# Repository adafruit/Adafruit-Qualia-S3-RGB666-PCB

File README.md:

## Adafruit Qualia ESP32-S3 for TTL RGB-666 Displays PCB

<a href="http://www.adafruit.com/products/5800"><br/>
Click here to purchase one from the Adafruit shop</a>

PCB files for the Adafruit Qualia ESP32-S3 for TTL RGB-666 Displays.

Format is EagleCAD schematic and board layout
* https://www.adafruit.com/product/5800

### Description

There's a few things everyone loves: ice cream, kittens, and honkin' large TFT screens. We're no strangers to small TFT's - [from our itsy 1.14" color display](https://www.adafruit.com/search?q=1.14+tft) that graces many-a-TFT-Feather to [our fancy 3.5" 320x480](https://www.adafruit.com/product/2050) breakout screen. But most people who dabble or engineer with microcontrollers know that you sort of 'top out' at 320x480 - that's the largest resolution you can use with every day SPI or 8-bit 8080 interfaces. After that, you're in TTL-interface TFT land, where displays no longer have an internal memory buffer and instead the controller has to continuously write scanline data over a 16 or 18 or 24 pin interface.

RGB TTL interface TFT displays can get big: they start out at around 4.3" diagonal 480x272, and can get to 800x480, 800x600 or even 720x720. For displays that big, you need a lot of video RAM (800x480 at 24 bit color is just over 1MB), plenty of spare GPIO to dedicate, and a peripheral that will DMA the video RAM out to the display continuously. This is a setup familiar to people working with hefty microcontrollers or microcomputers, the sort of device that run cell phones, or your car's GPS navigation screen. But until now, nearly impossible to use on low cost microcontrollers.

The ESP32-S3 is the first low-cost microcontroller that has a built in peripheral that can drive TTL displays, and can come with enough PSRAM to buffer those large images. For example, on the **Adafruit Qualia ESP32-S3 for TTL RGB-666 Displays**, we use a S3 module with 16 MB of Flash and 8 MB of octal PSRAM. Using the built in RGB display peripheral you can display graphics, images, animations or even video (cinepak, natch!) with near-instantaneous updates since the whole screen gets updated every ~30FPS.

This dev board is designed to make it easy for you to explore displays that use the "secondary standard' 40-pin RGB-666 connector. This pin order is most commonly seen on square, round and bar displays. [You'll want to compare the display you're using to this datasheet](https://cdn-shop.adafruit.com/product-files/5792/Specification_TL021WVC02CT-B1323B.pdf), if it matches you'll probably be good! One nice thing about this connector ordering is that it also includes pins for capacitive touch overlay, and we wire those up to the ESP32-S3's I2C port so you can also have touch control with your display.

**Don't forget! This is just the development board, a display is not included.** Use any RGB-666 pinout display with or without a touch overlay. Note that you will need to program in the driver initialization code, dimensions, and pulse widths in your programming language. Here are some known-working displays that you can use in Arduino or CircuitPython:

- [2.1" 480x480 Round with Capacitive Touch](https://www.adafruit.com/product/5792)
- [2.1" 480x480 Round without touch](https://www.adafruit.com/product/5806)
- [4" 720x720 Square with Capacitive Touch](https://www.adafruit.com/product/5794)
- [4" 720x720 Round without touch](https://www.adafruit.com/product/5793)
- [4.6" 960x320 Rectangular Bar](https://www.adafruit.com/product/5805)

On the Qualia board we have the S3 modules, with 16 pins connected to the TFT for 5-6-5 RGB color, plus HSync, VSync, Data Enable and Pixel Clock. There's a constant current backlight control circuit using the [TPS61169](https://www.ti.com/product/TPS61169/part-details/TPS61169DCKR) which can get up to 30V forward voltage and can be configured for 25mA-200mA in 25mA increments (default is 25mA). Power and programming is provided over a USB C connector, wired to the S3's native USB port. For debugging, the hardware UART TX pin is available as well.

Since almost every GPIO is used, and almost all RGB-666 displays need to be initialized over SPI, we put a [PCA9554](https://www.ti.com/product/PCA9554) I/O expander on the shared I2C bus. Arduino or CircuitPython can be instructed on how to use the expander to reset and init the display you have if necessary. The remaining expander pins are connected to two right-angle buttons, and the display backlight.

The expander is what lets us have a full 4-pin SPI port and two more analog GPIO pins - [enough to wire up an MMC in 1-wire SDIO mode along with an I2S amplifier to make an A/V playback demo](https://www.youtube.com/watch?v=pEjw-bCQ-lQ). Maybe we can even eat ice cream while watching kitten vids! There is also the shared I2C port, we provide a Stemma QT / Qwiic port for easy addition of any sensor or device you like.

### License

Adafruit invests time and resources providing this open source design, please support Adafruit and open-source hardware by purchasing products from [Adafruit](https://www.adafruit.com)!

Designed by Limor Fried/Ladyada for Adafruit Industries.

Creative Commons Attribution/Share-Alike, all text above must be included in any redistribution.
See license.txt for additional details.

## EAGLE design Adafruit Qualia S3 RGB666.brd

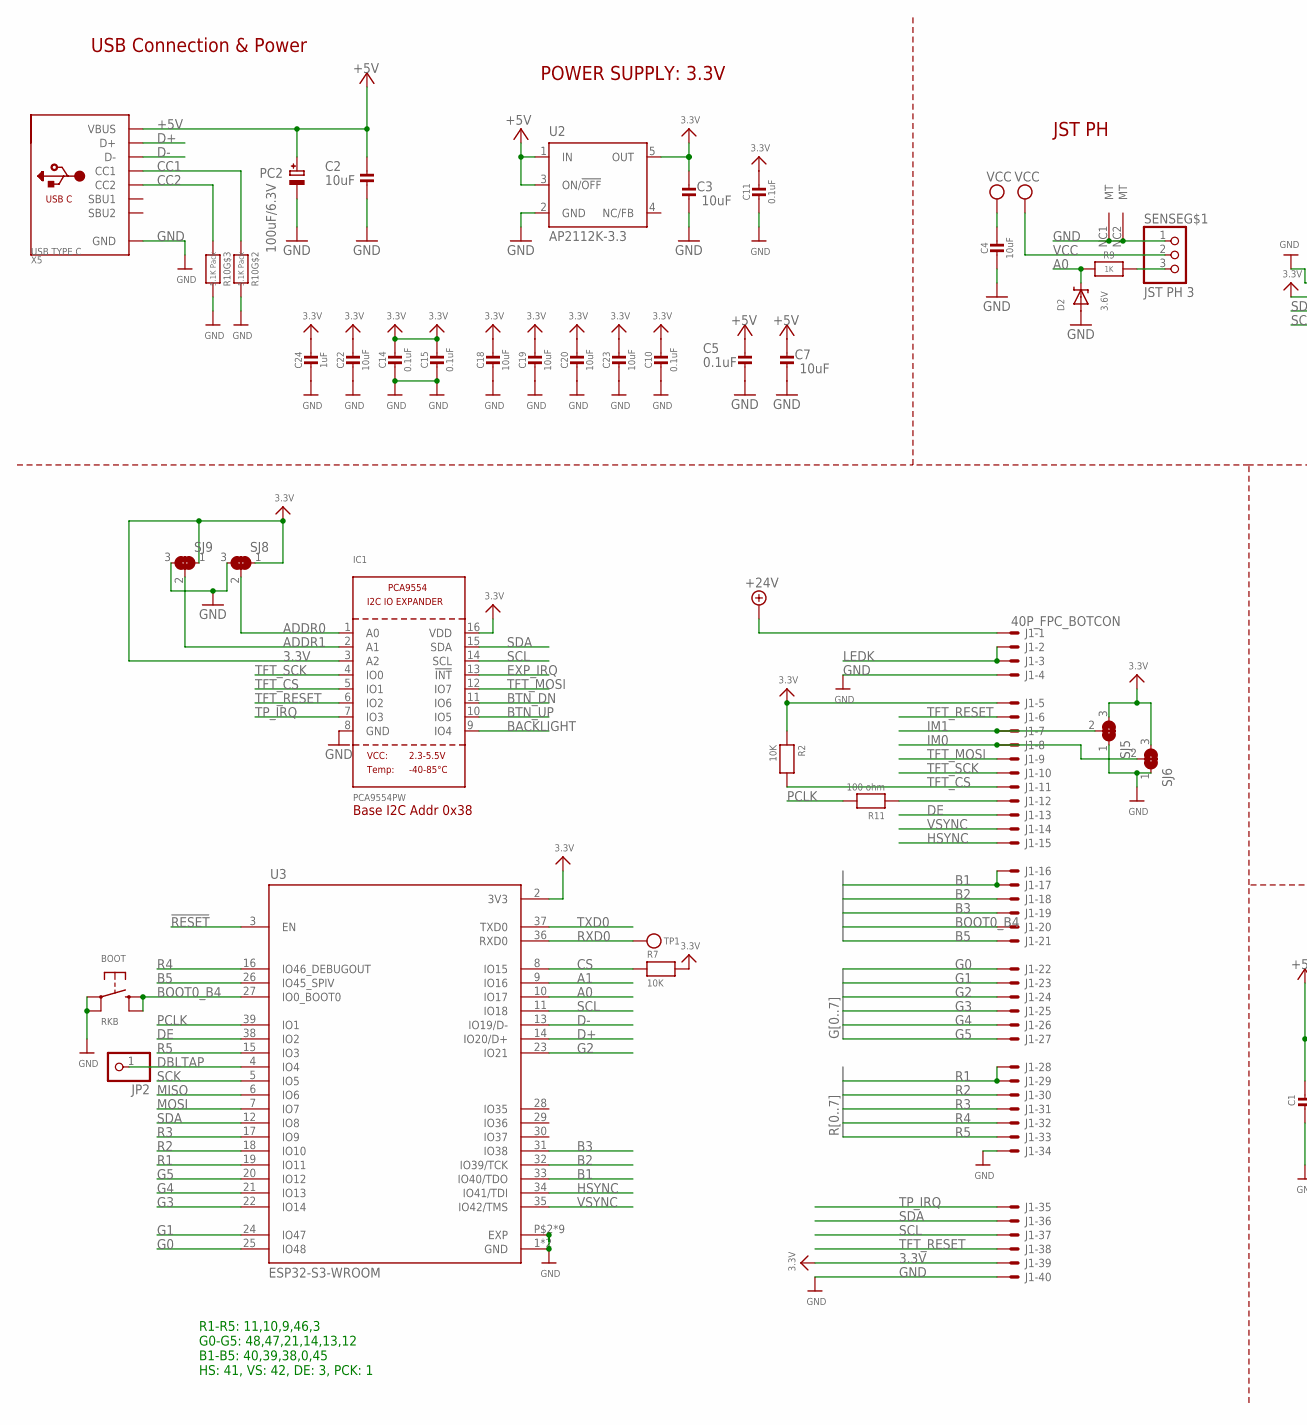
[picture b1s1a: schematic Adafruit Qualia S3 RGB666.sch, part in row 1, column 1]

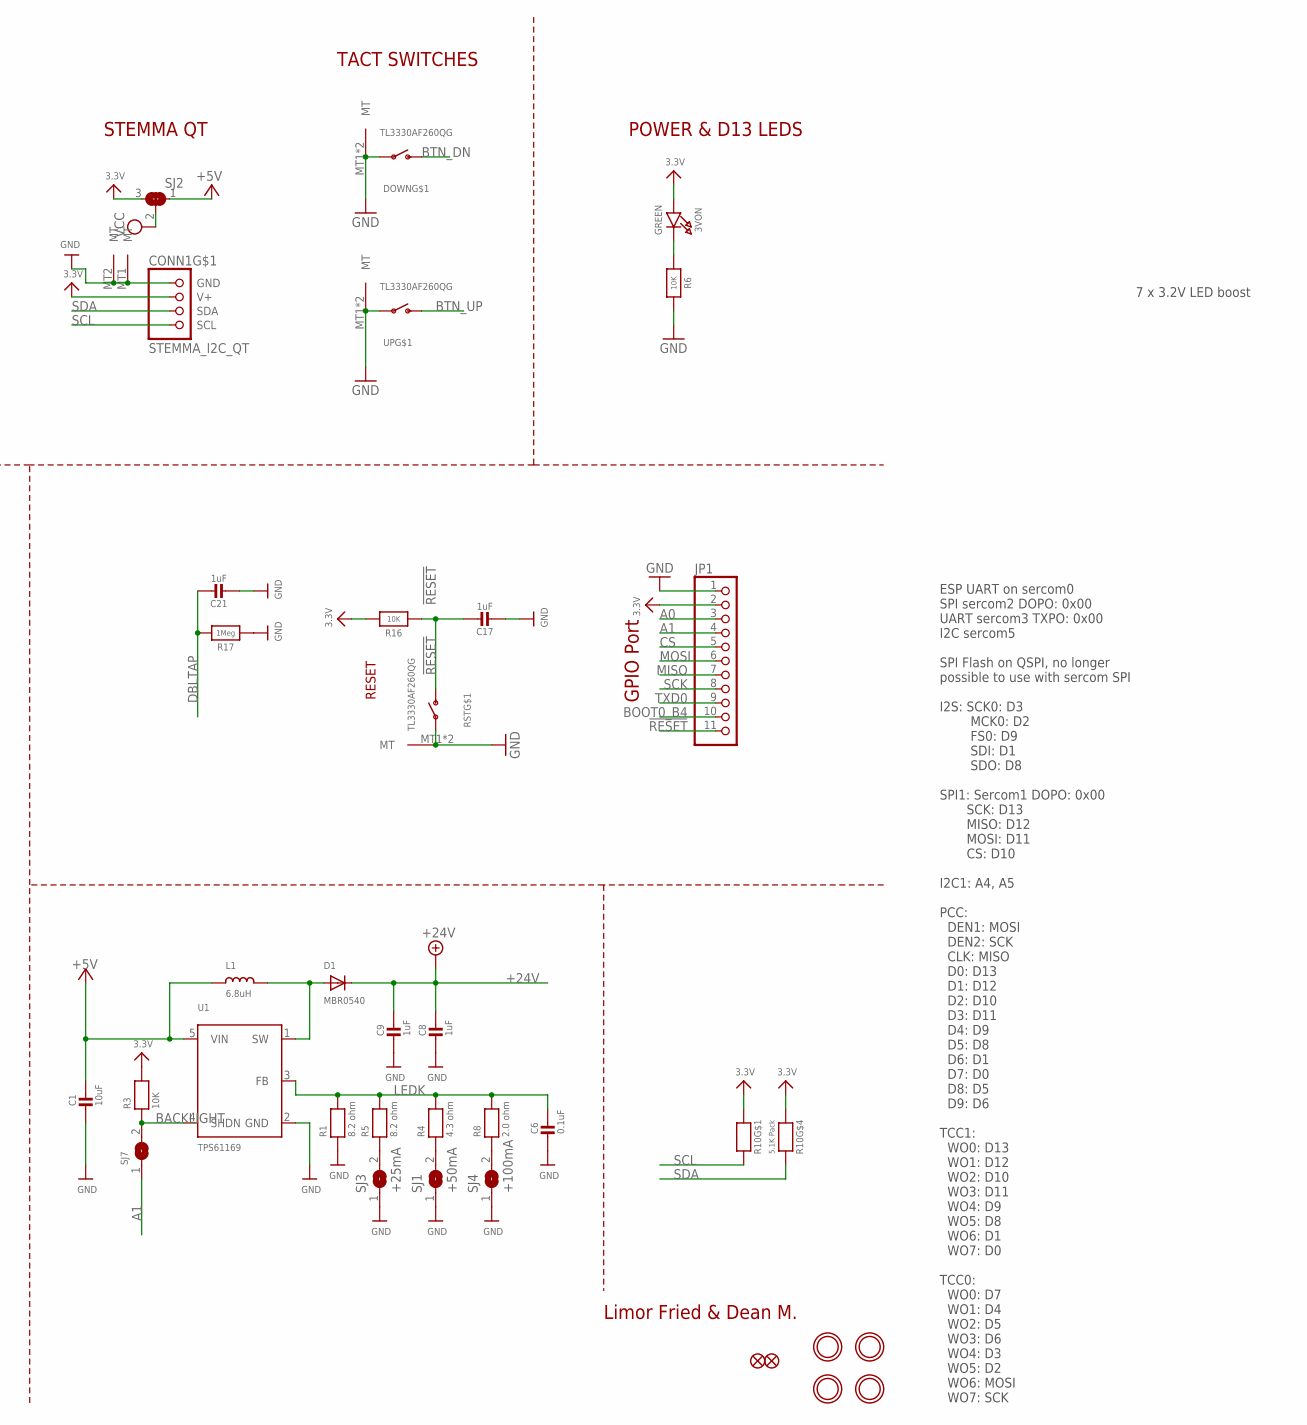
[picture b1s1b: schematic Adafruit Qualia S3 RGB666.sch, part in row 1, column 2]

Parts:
3VON: GREEN; CHIPLED_0603_NOOUTLINE
BOOT: RKB; BTN_RKB2_4.6X2.8
C1, C2, C3, C4, C7, C18, C19, C20, C22, C23: 10uF; 0805-NO
C5, C6, C10, C11, C14, C15: 0.1uF; 0603-NO
C8, C9, C17, C21, C24: 1uF; 0603-NO
CONN1: STEMMA_I2C_QT; JST_SH4
D1: MBR0540; SOD-123
D2: 3.6V; SOD-323
DOWN: TL3330AF260QG; SPST_TACTILE_RA
FID1, FID2: FIDUCIAL_1MM
IC1: PCA9554PW; TSSOP16
J1: 40P_FPC_BOTCON; FPC_40
JP1: HEADER-1X11; 1X11_ROUND
JP2: HEADER-1X1ROUND; 1X01_ROUND
L1: 6.8uH; INDUCTOR_5X5MM_NR5040_NOTHERMALS
PC2: 100uF/6.3V; PANASONIC_D
R1, R5: 8.2 ohm; 0603-NO
R2, R3, R6, R7, R16: 10K; 0603-NO
R4: 4.3 ohm; 0603-NO
R8: 2.0 ohm; 0603-NO
R9: 1K; 0603-NO
R10: 5.1K Pack; RESPACK_4X0603
R11: 100 ohm; 0603-NO
R17: 1Meg; 0603-NO
RST: TL3330AF260QG; SPST_TACTILE_RA
SENSE: JST PH 3; JSTPH3
SJ1: +50mA; SOLDERJUMPER_ARROW_NOPASTE
SJ2, SJ5, SJ6, SJ8, SJ9: SOLDERJUMPER_2WAY; SOLDERJUMPER_2WAY_OPEN_NOPASTE
SJ3: +25mA; SOLDERJUMPER_ARROW_NOPASTE
SJ4: +100mA; SOLDERJUMPER_ARROW_NOPASTE
SJ7: SOLDERJUMPER; SOLDERJUMPER_ARROW_NOPASTE
TP1: TESTPOINTROUND1.5MMNO; TESTPOINT_ROUND_1.5MM_NO
U1: TPS61169; SC70-5
U2: AP2112K-3.3; SOT23-DBV
U3: ESP32-S3-WROOM; S3-WROOM32
U$14, U$19, U$22, U$24: MOUNTINGHOLE2.5; MOUNTINGHOLE_2.5_PLATED
UP: TL3330AF260QG; SPST_TACTILE_RA
X5: USB TYPE C; USB_C_CUSB31-CFM2AX-01-X

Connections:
3.3V: 3VON.A, C3.2, C10.2, C11.2, C14.2, C15.2, C18.1, C19.1, C20.1, C22.1, C23.1, C24.1, CONN1.2 (V+), IC1.3 (A2), IC1.16 (VDD), J1.5 (MS), J1.39 (MS), JP1.2, R2.1, R3.2, R7.2, R10.1, R10.4 (1), R16.2, SJ2.3, SJ5.3, SJ6.3, SJ8.1, SJ9.1, U2.5 (OUT), U3.2 (3V3)
!RESET: C17.1, JP1.11, R16.1, RST.2 (S), U3.3 (EN)
+5V: C1.1, C2.2, C5.2, C7.2, L1.P$1 (1), PC2.+, SJ2.1, U1.5 (VIN), U2.1 (IN), U2.3 (ON/!OFF), X5.A4B9 (VBUS), X5.B4A9 (VBUS)
+24V: C8.1, C9.1, D1.C, J1.1 (MSV)
A0: D2.C, JP1.3, R9.2, U3.10 (IO17)
A0_JST: R9.1, SENSE.3
A1: JP1.4, SJ7.1, U3.9 (IO16)
ADDR0: IC1.1 (A0), SJ8.2
ADDR1: IC1.2 (A1), SJ9.2
B1: J1.16 (MS), J1.17 (MS), U3.33 (IO40/TDO)
B2: J1.18 (MS), U3.32 (IO39/TCK)
B3: J1.19 (MS), U3.31 (IO38)
B5: J1.21 (MS), U3.26 (IO45_SPIV)
BACKLIGHT: IC1.9 (IO4), R3.1, SJ7.2, U1.4 (SHDN)
BOOT0_B4: BOOT.B (S), BOOT.B' (S1), J1.20 (MS), JP1.10, U3.27 (IO0_BOOT0)
BTN_DN: DOWN.2 (S), IC1.11 (IO6)
BTN_UP: IC1.10 (IO5), UP.2 (S)
CC1: R10.2 (1), X5.A5 (CC1)
CC2: R10.3 (1), X5.B5 (CC2)
CS: JP1.5, R7.1, U3.8 (IO15)
D+: U3.14 (IO20/D+), X5.A6 (D+), X5.B6 (D+)
D-: U3.13 (IO19/D-), X5.A7 (D-), X5.B7 (D-)
DBLTAP: C21.1, JP2.1, R17.2, U3.4 (IO4)
DE: J1.13 (MS), U3.38 (IO2)
EXP_IRQ: IC1.13 (!INT)
G0: J1.22 (MS), U3.25 (IO48)
G1: J1.23 (MS), U3.24 (IO47)
G2: J1.24 (MS), U3.23 (IO21)
G3: J1.25 (MS), U3.22 (IO14)
G4: J1.26 (MS), U3.21 (IO13)
G5: J1.27 (MS), U3.20 (IO12)
GND: BOOT.A, BOOT.A' (P1), C1.2, C2.1, C3.1, C4.2, C5.1, C6.2, C7.1, C8.2, C9.2, C10.1, C11.1, C14.1, C15.1, C17.2, C18.2, C19.2, C20.2, C21.2, C22.2, C23.2, C24.2, CONN1.1 (GND), CONN1.MT1 (MT), CONN1.MT2 (MT), D2.A, DOWN.1, DOWN.MT1 (MT), DOWN.MT2 (MT), IC1.8 (GND), J1.4 (MS), J1.34 (MS), J1.40 (MS), JP1.1, PC2.-, R1.1, R6.2, R10.6 (2), R10.7 (2), R17.1, RST.1, RST.MT1 (MT), RST.MT2 (MT), SENSE.1, SENSE.NC1 (MT), SENSE.NC2 (MT), SJ1.1, SJ3.1, SJ4.1, SJ5.1, SJ6.1, SJ8.3, SJ9.3, U1.2 (GND), U2.2 (GND), U3.1 (GND), U3.40 (GND), U3.P$2 (EXP), U3.P$3 (EXP), U3.P$4 (EXP), U3.P$5 (EXP), U3.P$6 (EXP), U3.P$7 (EXP), U3.P$8 (EXP), U3.P$9 (EXP), U3.P$10 (EXP), UP.1, UP.MT1 (MT), UP.MT2 (MT), X5.A1B12 (GND), X5.B1A12 (GND)
HSYNC: J1.15 (MS), U3.34 (IO41/TDI)
IM0: J1.8 (MS), SJ6.2
IM1: J1.7 (MS), SJ5.2
LEDK: C6.1, J1.2 (MS), J1.3 (MS), R1.2, R4.2, R5.2, R8.2, U1.3 (FB)
MISO: JP1.7, U3.6 (IO6)
MOSI: JP1.6, U3.7 (IO7)
unnamed: 3VON.C, R6.1
unnamed: R4.1, SJ1.2
unnamed: J1.12 (MS), R11.1
unnamed: D1.A, L1.P$2 (2), U1.1 (SW)
unnamed: R5.1, SJ3.2
unnamed: R8.1, SJ4.2
PCLK: R11.2, U3.39 (IO1)
R1: J1.28 (MS), J1.29 (MS), U3.19 (IO11)
R2: J1.30 (MS), U3.18 (IO10)
R3: J1.31 (MS), U3.17 (IO9)
R4: J1.32 (MS), U3.16 (IO46_DEBUGOUT)
R5: J1.33 (MS), U3.15 (IO3)
RXD0: TP1.P$1, U3.36 (RXD0)
SCK: JP1.8, U3.5 (IO5)
SCL: CONN1.4 (SCL), IC1.14 (SCL), J1.37 (MS), R10.8 (2), U3.11 (IO18)
SDA: CONN1.3 (SDA), IC1.15 (SDA), J1.36 (MS), R10.5 (2), U3.12 (IO8)
TFT_CS: IC1.5 (IO1), J1.11 (MS), R2.2
TFT_MOSI: IC1.12 (IO7), J1.9 (MS)
TFT_RESET: IC1.6 (IO2), J1.6 (MS), J1.38 (MS)
TFT_SCK: IC1.4 (IO0), J1.10 (MS)
TP_IRQ: IC1.7 (IO3), J1.35 (MS)
TXD0: JP1.9, U3.37 (TXD0)
VCC: C4.1, SENSE.2, SJ2.2
VSYNC: J1.14 (MS), U3.35 (IO42/TMS)

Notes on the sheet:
Limor Fried & Dean M.
USB Connection & Power
POWER SUPPLY: 3.3V
POWER & D13 LEDS
GPIO Port
ESP UART on sercom0 SPI sercom2 DOPO: 0x00 UART sercom3 TXPO: 0x00 I2C sercom5 SPI Flash on QSPI, no longer possible to use with sercom SPI I2S: SCK0: D3 MCK0: D2 FS0: D9 SDI: D1 SDO: D8 SPI1: Sercom1 DOPO: 0x00 SCK: D13 MISO: D12 MOSI: D11 CS: D10 I2C1: A4, A5 PCC: DEN1: MOSI DEN2: SCK CLK: MISO D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
RESET
JST PH
STEMMA QT
TACT SWITCHES
7 x 3.2V LED boost
Base I2C Addr 0x38
R1-R5: 11,10,9,46,3 G0-G5: 48,47,21,14,13,12 B1-B5: 40,39,38,0,45 HS: 41, VS: 42, DE: 3, PCK: 1

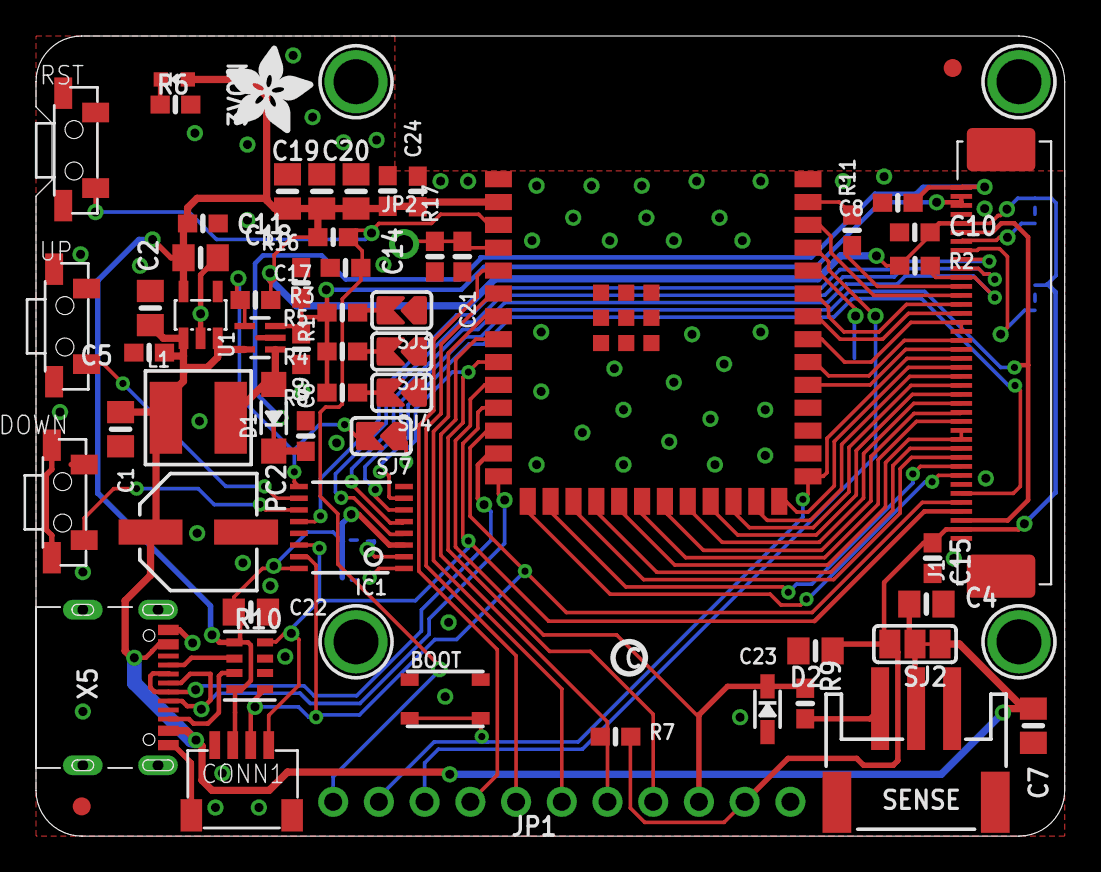
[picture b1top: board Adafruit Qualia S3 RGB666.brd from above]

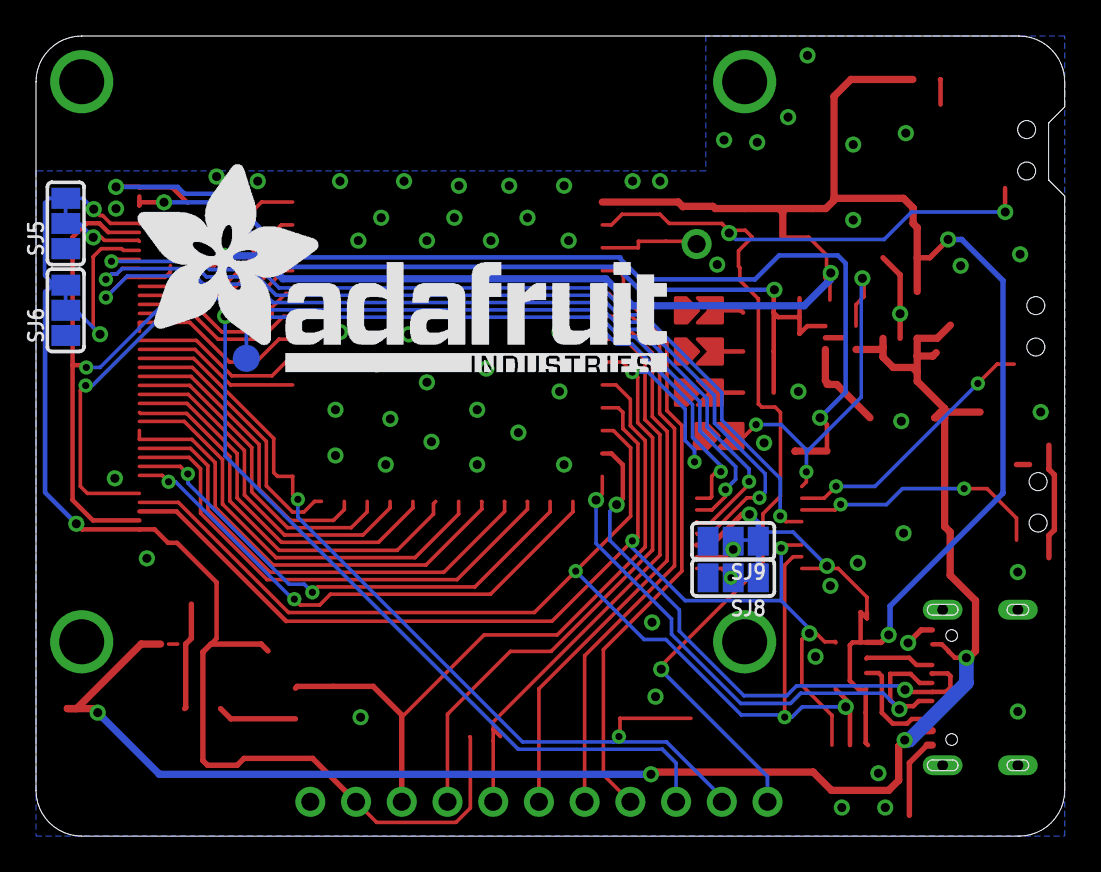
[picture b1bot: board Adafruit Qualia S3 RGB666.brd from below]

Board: 2 copper layers, 57.1 x 44.5 mm, 112 parts (19 on the bottom side), 61 nets.

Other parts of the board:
PLABEL0: PLABEL0
PLABEL1: PLABEL1
PLABEL2: PLABEL2
PLABEL3: PLABEL3
PLABEL4: PLABEL4
PLABEL5: PLABEL5
PLABEL6: PLABEL6
PLABEL7: PLABEL7
PLABEL8: PLABEL8
PLABEL9: PLABEL9
PLABEL10: PLABEL10
PLABEL11: PLABEL11
PLABEL12: PLABEL12
PLABEL13: PLABEL13
PLABEL14: PLABEL14
PLABEL15: PLABEL15
PLABEL16: PLABEL16
PLABEL17: PLABEL17
PLABEL18: PLABEL18
PLABEL19: PLABEL19
PLABEL20: PLABEL20
PLABEL21: PLABEL21
PLABEL22: PLABEL22
PLABEL23: PLABEL23
PLABEL24: PLABEL24
PLABEL25: PLABEL25
PLABEL26: PLABEL26
PLABEL27: PLABEL27
PLABEL28: PLABEL28
PLABEL29: PLABEL29
PLABEL30: PLABEL30
PLABEL31: PLABEL31
PLABEL32: PLABEL32
PLABEL33: PLABEL33
PLABEL34: PLABEL34
PLABEL35: PLABEL35
PLABEL36: PLABEL36
PLABEL37: PLABEL37
PLABEL38: PLABEL38
PLABEL39: PLABEL39
U$44: PCBFEAT-REV-040
U$46: ADAFRUIT_5MM
U$49: ADAFRUIT_TEXT_30MM

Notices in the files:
parts and their libraries:
microbuilder: This work is placed in the public domain, and may be freely used for commercial and non-commercial work with the following conditions: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
SparkFun-Aesthetics: Licensing: CC v3.0 Share-Alike You are welcome to use this library for commercial purposes.
